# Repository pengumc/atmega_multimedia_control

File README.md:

An atmega based usb hid consumer decive for volume, pause/play, next and previous functions
===========================================================================================

see also [http://www.pengurobotics.com/projects/media_controller](http://www.pengurobotics.com/projects/media_controller)

and [http://www.thingiverse.com/thing:126130](http://www.thingiverse.com/thing:126130) for the 3D files

Building the firmware
---------------------
you need the vusb files from 
https://github.com/obdev/v-usb or http://www.obdev.at/products/vusb/download.html

more specifically: the "usbdrv" folder needs to be copied to your cloned repository.

step by step example:

clone this repository

    git clone https://github.com/pengumc/atmega_multimedia_control

grab the vusb files    

    wget http://www.obdev.at/downloads/vusb/vusb-20121206.tar.gz

extract

    tar -xf vusb-20121206.tar.gz

cp the usbdrv folder to the cloned repository

    cp -r vusb-20121206/usbdrv atmega_multimedia_control/
    
build firmware

    cd atmega_multimedia_control
    make

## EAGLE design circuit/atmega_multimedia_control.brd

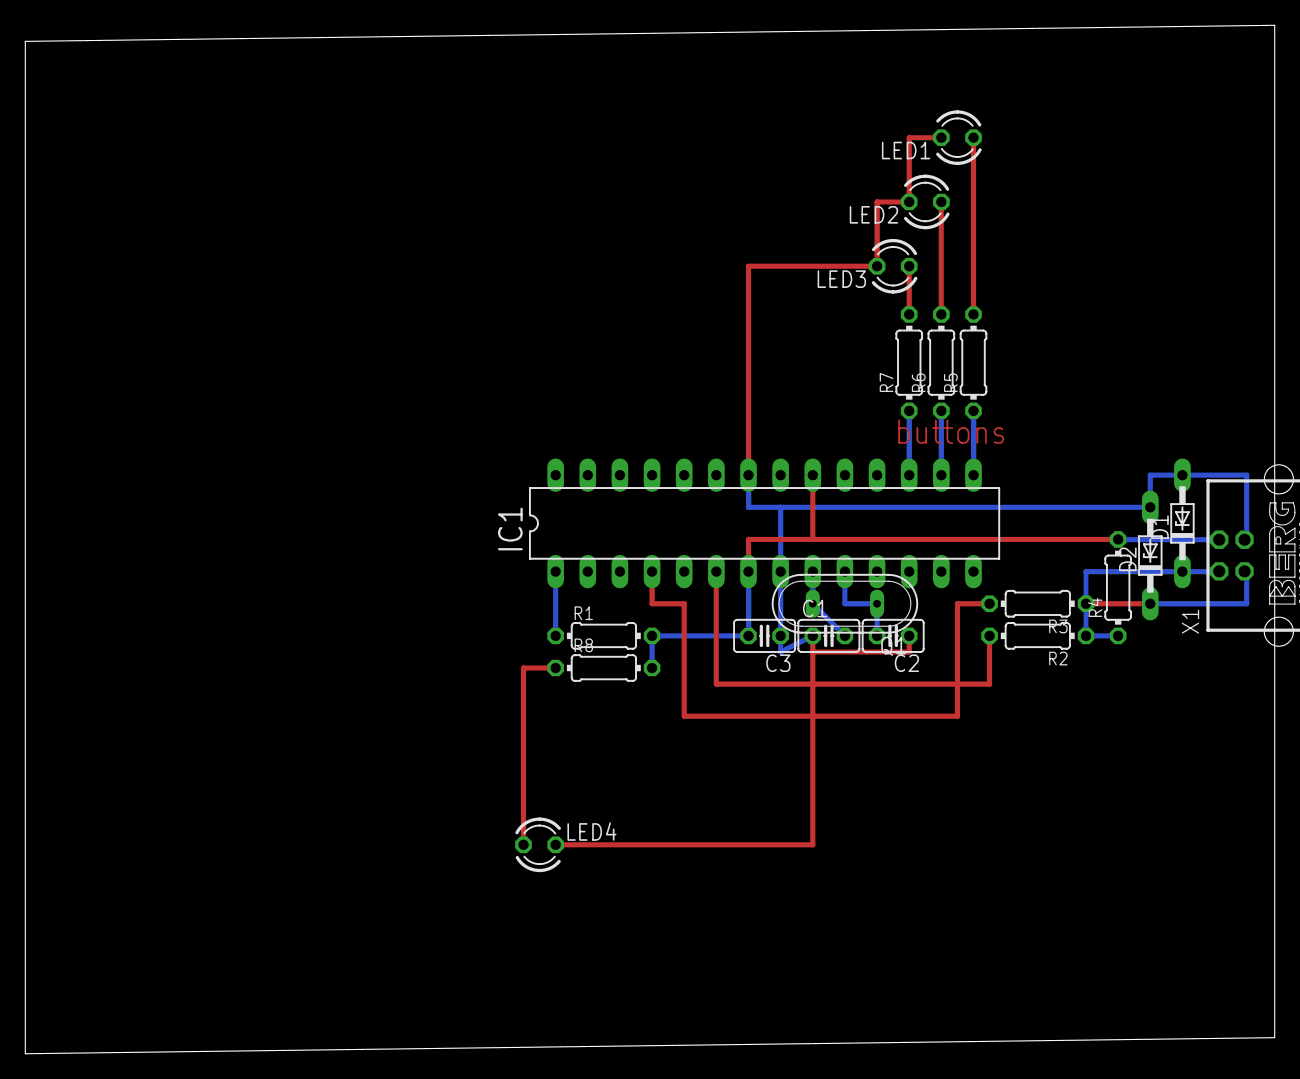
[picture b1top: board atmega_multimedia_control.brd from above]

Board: 2 copper layers, 98.7 x 81.3 mm, 20 parts (0 on the bottom side), 16 nets.

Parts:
C1, C2: 22p; C025-025X050
C3: 100n; C025-025X050
D1, D2: 3v6; DO34Z7
IC1: MEGA8-P; DIL28-3
LED1, LED2, LED3, LED4: LED3MM
Q1: 20Mhz; QS
R1: 100k; 0204/7
R2, R3: 68; 0204/7
R4, R5, R6, R7, R8: 2k2; 0204/7
X1: USB; PN61729

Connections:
GND: C1.1, C2.1, C3.1, D1.A, D2.A, IC1.8, IC1.22, LED1.K, LED2.K, LED3.K, LED4.K, X1.4
unnamed: IC1.1, R1.1
unnamed: C1.2, IC1.9, Q1.2
unnamed: C2.2, IC1.10, Q1.1
unnamed: D2.C, R3.1, X1.3
unnamed: IC1.6, R2.2
unnamed: IC1.4, R3.2
unnamed: IC1.15, R5.1
unnamed: LED1.A, R5.2
unnamed: IC1.16, R6.1
unnamed: LED2.A, R6.2
unnamed: IC1.17, R7.1
unnamed: LED3.A, R7.2
unnamed: LED4.A, R8.1
unnamed: D1.C, R2.1, R4.1, X1.2
VCC: C3.2, IC1.7, IC1.20, R1.2, R4.2, R8.2, X1.1

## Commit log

2013-06-25 start
2013-06-25 updated hid descriptor
2013-06-25 start of circuit
2013-06-27 pc-side and working volume knob
    the amount that the volume is changed when volume up or down is sent,
    differs per distro. windows tends to use 2/100, most linux 10/100
2013-06-28 updated circuit
2013-06-30 3 buttons + know working
    undocumented usage 0xcd is for play/pause
2013-07-05 formatting
2013-07-06 circuit and board done
    volume knob is missing from board. some led resistors still need proper
    placement, will sort that out during soldering
2013-07-06 circuit image
2013-07-21 soldering done
2013-07-21 no wip
2013-07-26 rc 1
2013-07-26 rc 2
2013-07-31 visual updates
2013-07-31 formatting + comments
2013-07-31 more comments
2014-07-26 fixed schematic
2014-11-04 added build instructions
2014-11-04 updated pic
2014-11-15 filtered adc
